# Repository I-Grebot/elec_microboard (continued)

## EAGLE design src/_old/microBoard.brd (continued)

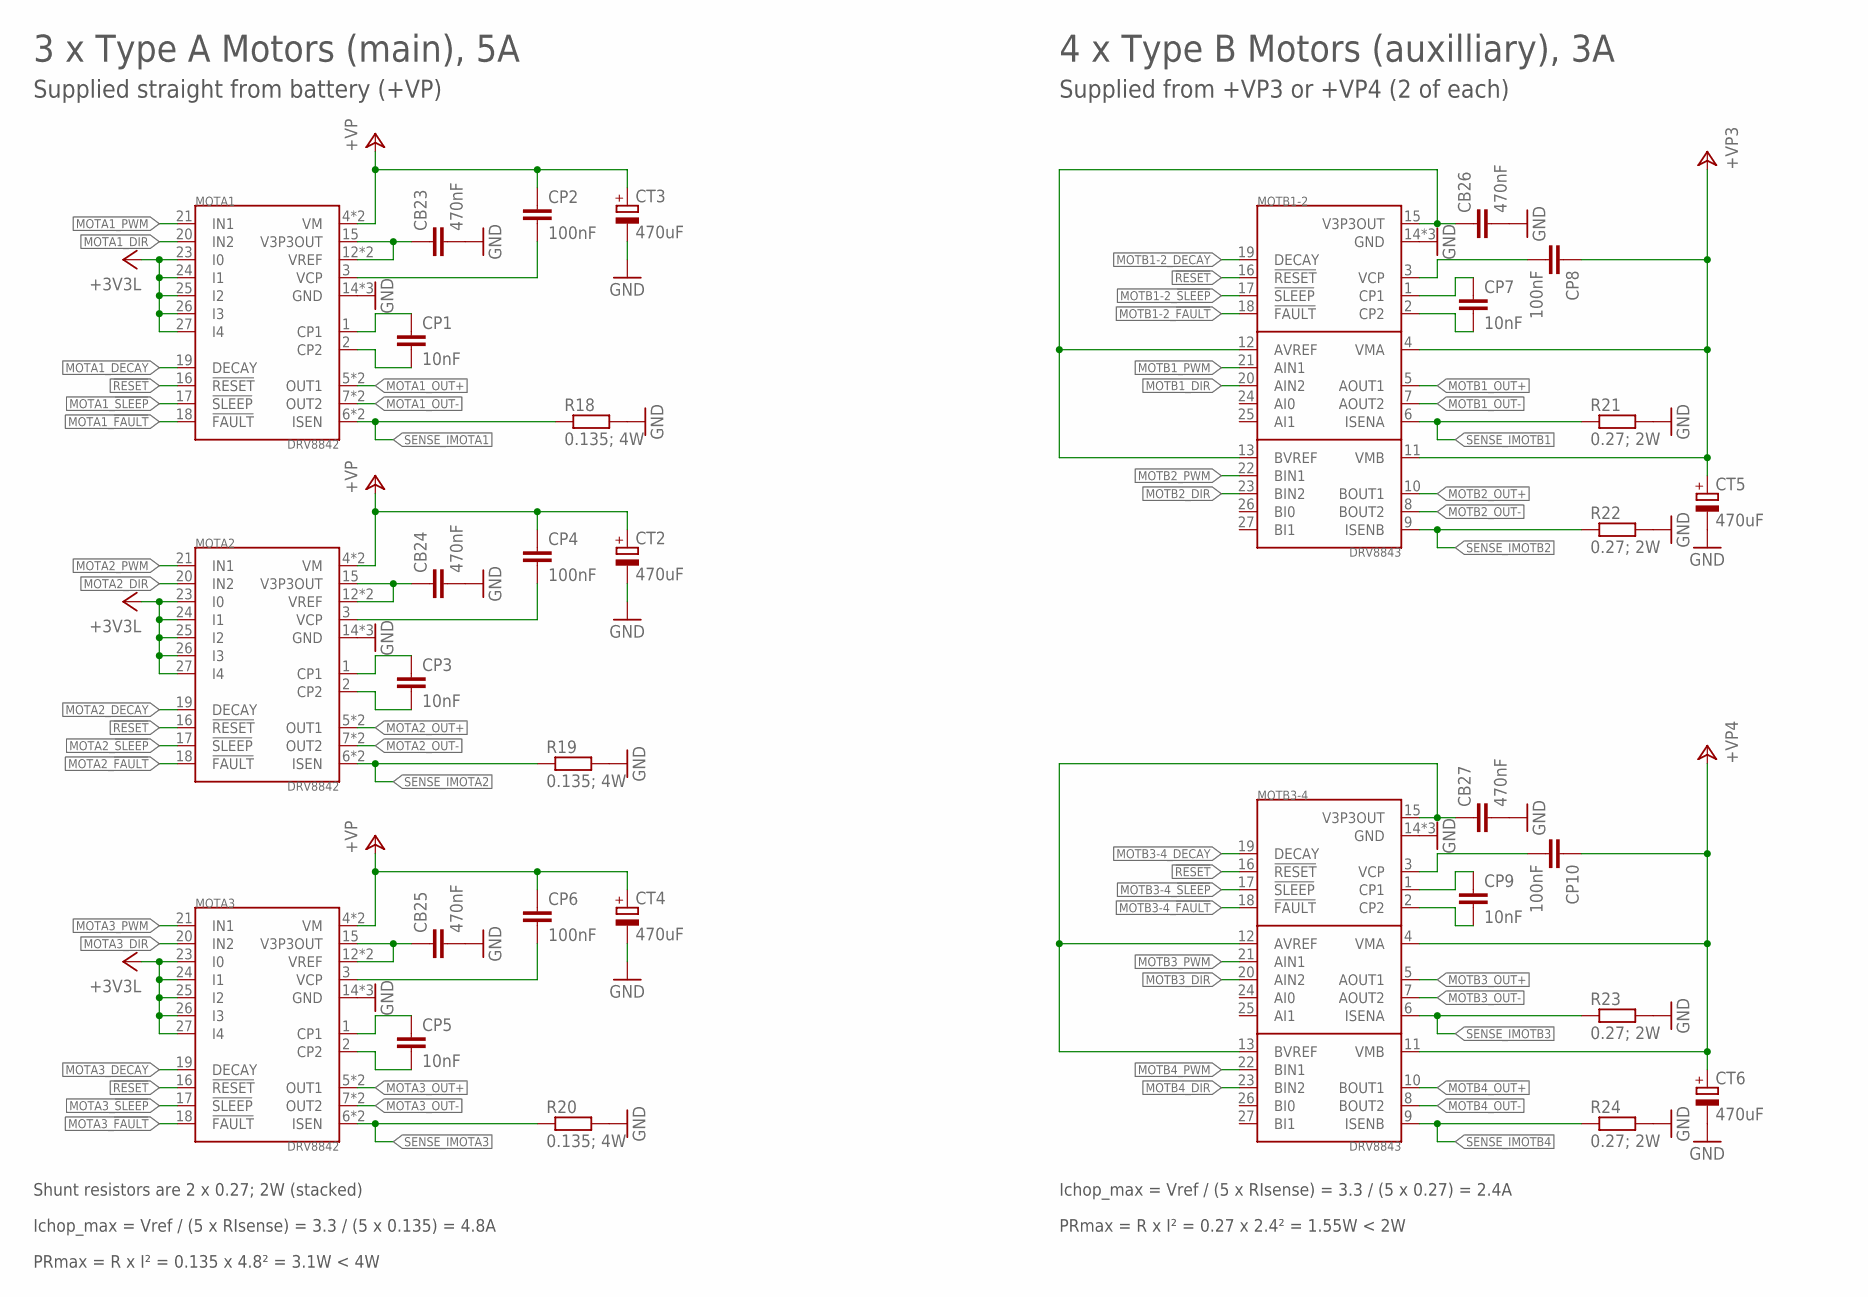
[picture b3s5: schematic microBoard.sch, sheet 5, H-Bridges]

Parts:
CB23, CB24, CB25, CB26, CB27: 470nF; C0603
CP1, CP3, CP5, CP7, CP9: 10nF; C0603
CP2, CP4, CP6, CP8, CP10: 100nF; C0603
CT2, CT3, CT4, CT5, CT6: 470uF; PANASONIC_D
MOTA1, MOTA2, MOTA3: DRV8842; PWP_28
MOTB1-2, MOTB3-4: DRV8843; PWP_28
R18, R19, R20: 0.135; 4W; R2512
R21, R22, R23, R24: 0.27; 2W; R2512

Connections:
!RESET!: MOTA1.16 (!RESET!), MOTA2.16 (!RESET!), MOTA3.16 (!RESET!), MOTB1-2.16 (!RESET!), MOTB3-4.16 (!RESET!)
+3V3L: MOTA1.23 (I0), MOTA1.24 (I1), MOTA1.25 (I2), MOTA1.26 (I3), MOTA1.27 (I4), MOTA2.23 (I0), MOTA2.24 (I1), MOTA2.25 (I2), MOTA2.26 (I3), MOTA2.27 (I4), MOTA3.23 (I0), MOTA3.24 (I1), MOTA3.25 (I2), MOTA3.26 (I3), MOTA3.27 (I4); also elsewhere on the board
+VP: CP2.1, CP4.1, CP6.1, CT2.+, CT3.+, CT4.+, MOTA1.4 (VM), MOTA1.11 (VM), MOTA2.4 (VM), MOTA2.11 (VM), MOTA3.4 (VM), MOTA3.11 (VM); also elsewhere on the board
+VP3: CP8.1, CT5.+, MOTB1-2.4 (VMA), MOTB1-2.11 (VMB); also elsewhere on the board
+VP4: CP10.1, CT6.+, MOTB3-4.4 (VMA), MOTB3-4.11 (VMB); also elsewhere on the board
GND: CB23.2, CB24.2, CB25.2, CB26.2, CB27.2, CT2.-, CT3.-, CT4.-, CT5.-, CT6.-, MOTA1.14 (GND), MOTA1.28 (GND), MOTA1.PPAD (GND), MOTA2.14 (GND), MOTA2.28 (GND), MOTA2.PPAD (GND), MOTA3.14 (GND), MOTA3.28 (GND), MOTA3.PPAD (GND), MOTB1-2.14 (GND), MOTB1-2.28 (GND), MOTB1-2.PPAD (GND), MOTB3-4.14 (GND), MOTB3-4.28 (GND), MOTB3-4.PPAD (GND), R18.2, R19.2, R20.2, R21.2, R22.2, R23.2, R24.2; also elsewhere on the board
MOTA1_!FAULT!: MOTA1.18 (!FAULT!); also elsewhere on the board
MOTA1_!SLEEP!: MOTA1.17 (!SLEEP!)
MOTA1_DECAY: MOTA1.19 (DECAY)
MOTA1_DIR: MOTA1.20 (IN2)
MOTA1_OUT+: MOTA1.5 (OUT1), MOTA1.10 (OUT1)
MOTA1_OUT-: MOTA1.7 (OUT2), MOTA1.8 (OUT2)
MOTA1_PWM: MOTA1.21 (IN1); also elsewhere on the board
MOTA2_!FAULT!: MOTA2.18 (!FAULT!); also elsewhere on the board
MOTA2_!SLEEP!: MOTA2.17 (!SLEEP!)
MOTA2_DECAY: MOTA2.19 (DECAY)
MOTA2_DIR: MOTA2.20 (IN2)
MOTA2_OUT+: MOTA2.5 (OUT1), MOTA2.10 (OUT1)
MOTA2_OUT-: MOTA2.7 (OUT2), MOTA2.8 (OUT2)
MOTA2_PWM: MOTA2.21 (IN1); also elsewhere on the board
MOTA3_!FAULT!: MOTA3.18 (!FAULT!); also elsewhere on the board
MOTA3_!SLEEP!: MOTA3.17 (!SLEEP!)
MOTA3_DECAY: MOTA3.19 (DECAY)
MOTA3_DIR: MOTA3.20 (IN2)
MOTA3_OUT+: MOTA3.5 (OUT1), MOTA3.10 (OUT1)
MOTA3_OUT-: MOTA3.7 (OUT2), MOTA3.8 (OUT2)
MOTA3_PWM: MOTA3.21 (IN1); also elsewhere on the board
MOTB1-2_!FAULT!: MOTB1-2.18 (!FAULT!); also elsewhere on the board
MOTB1-2_!SLEEP!: MOTB1-2.17 (!SLEEP!)
MOTB1-2_DECAY: MOTB1-2.19 (DECAY)
MOTB1_DIR: MOTB1-2.20 (AIN2)
MOTB1_OUT+: MOTB1-2.5 (AOUT1)
MOTB1_OUT-: MOTB1-2.7 (AOUT2)
MOTB1_PWM: MOTB1-2.21 (AIN1); also elsewhere on the board
MOTB2_DIR: MOTB1-2.23 (BIN2)
MOTB2_OUT+: MOTB1-2.10 (BOUT1)
MOTB2_OUT-: MOTB1-2.8 (BOUT2)
MOTB2_PWM: MOTB1-2.22 (BIN1); also elsewhere on the board
MOTB3-4_!FAULT!: MOTB3-4.18 (!FAULT!); also elsewhere on the board
MOTB3-4_!SLEEP!: MOTB3-4.17 (!SLEEP!)
MOTB3-4_DECAY: MOTB3-4.19 (DECAY)
MOTB3_DIR: MOTB3-4.20 (AIN2)
MOTB3_OUT+: MOTB3-4.5 (AOUT1)
MOTB3_OUT-: MOTB3-4.7 (AOUT2)
MOTB3_PWM: MOTB3-4.21 (AIN1); also elsewhere on the board
MOTB4_DIR: MOTB3-4.23 (BIN2)
MOTB4_OUT+: MOTB3-4.10 (BOUT1)
MOTB4_OUT-: MOTB3-4.8 (BOUT2)
MOTB4_PWM: MOTB3-4.22 (BIN1); also elsewhere on the board
unnamed: CP3.1, MOTA2.1 (CP1)
unnamed: CP3.2, MOTA2.2 (CP2)
unnamed: CP1.1, MOTA1.1 (CP1)
unnamed: CP1.2, MOTA1.2 (CP2)
unnamed: CP2.2, MOTA1.3 (VCP)
unnamed: CB23.1, MOTA1.12 (VREF), MOTA1.13 (VREF), MOTA1.15 (V3P3OUT)
unnamed: CP4.2, MOTA2.3 (VCP)
unnamed: CB24.1, MOTA2.12 (VREF), MOTA2.13 (VREF), MOTA2.15 (V3P3OUT)
unnamed: CP5.1, MOTA3.1 (CP1)
unnamed: CP5.2, MOTA3.2 (CP2)
unnamed: CP6.2, MOTA3.3 (VCP)
unnamed: CB25.1, MOTA3.12 (VREF), MOTA3.13 (VREF), MOTA3.15 (V3P3OUT)
unnamed: CP7.2, MOTB1-2.2 (CP2)
unnamed: CP7.1, MOTB1-2.1 (CP1)
unnamed: CP8.2, MOTB1-2.3 (VCP)
unnamed: CB26.1, MOTB1-2.12 (AVREF), MOTB1-2.13 (BVREF), MOTB1-2.15 (V3P3OUT)
unnamed: CP9.2, MOTB3-4.2 (CP2)
unnamed: CP9.1, MOTB3-4.1 (CP1)
unnamed: CP10.2, MOTB3-4.3 (VCP)
unnamed: CB27.1, MOTB3-4.12 (AVREF), MOTB3-4.13 (BVREF), MOTB3-4.15 (V3P3OUT)
SENSE_IMOTA1: MOTA1.6 (ISEN), MOTA1.9 (ISEN), R18.1; also elsewhere on the board
SENSE_IMOTA2: MOTA2.6 (ISEN), MOTA2.9 (ISEN), R19.1; also elsewhere on the board
SENSE_IMOTA3: MOTA3.6 (ISEN), MOTA3.9 (ISEN), R20.1; also elsewhere on the board
SENSE_IMOTB1: MOTB1-2.6 (ISENA), R21.1; also elsewhere on the board
SENSE_IMOTB2: MOTB1-2.9 (ISENB), R22.1; also elsewhere on the board
SENSE_IMOTB3: MOTB3-4.6 (ISENA), R23.1; also elsewhere on the board
SENSE_IMOTB4: MOTB3-4.9 (ISENB), R24.1; also elsewhere on the board

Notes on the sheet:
3 x Type A Motors (main), 5A
Ichop_max = Vref / (5 x RIsense) = 3.3 / (5 x 0.135) = 4.8A
Ichop_max = Vref / (5 x RIsense) = 3.3 / (5 x 0.27) = 2.4A
PRmax = R x I² = 0.27 x 2.4² = 1.55W < 2W
PRmax = R x I² = 0.135 x 4.8² = 3.1W < 4W
Shunt resistors are 2 x 0.27; 2W (stacked)
4 x Type B Motors (auxilliary), 3A
Supplied straight from battery (+VP)
Supplied from +VP3 or +VP4 (2 of each)

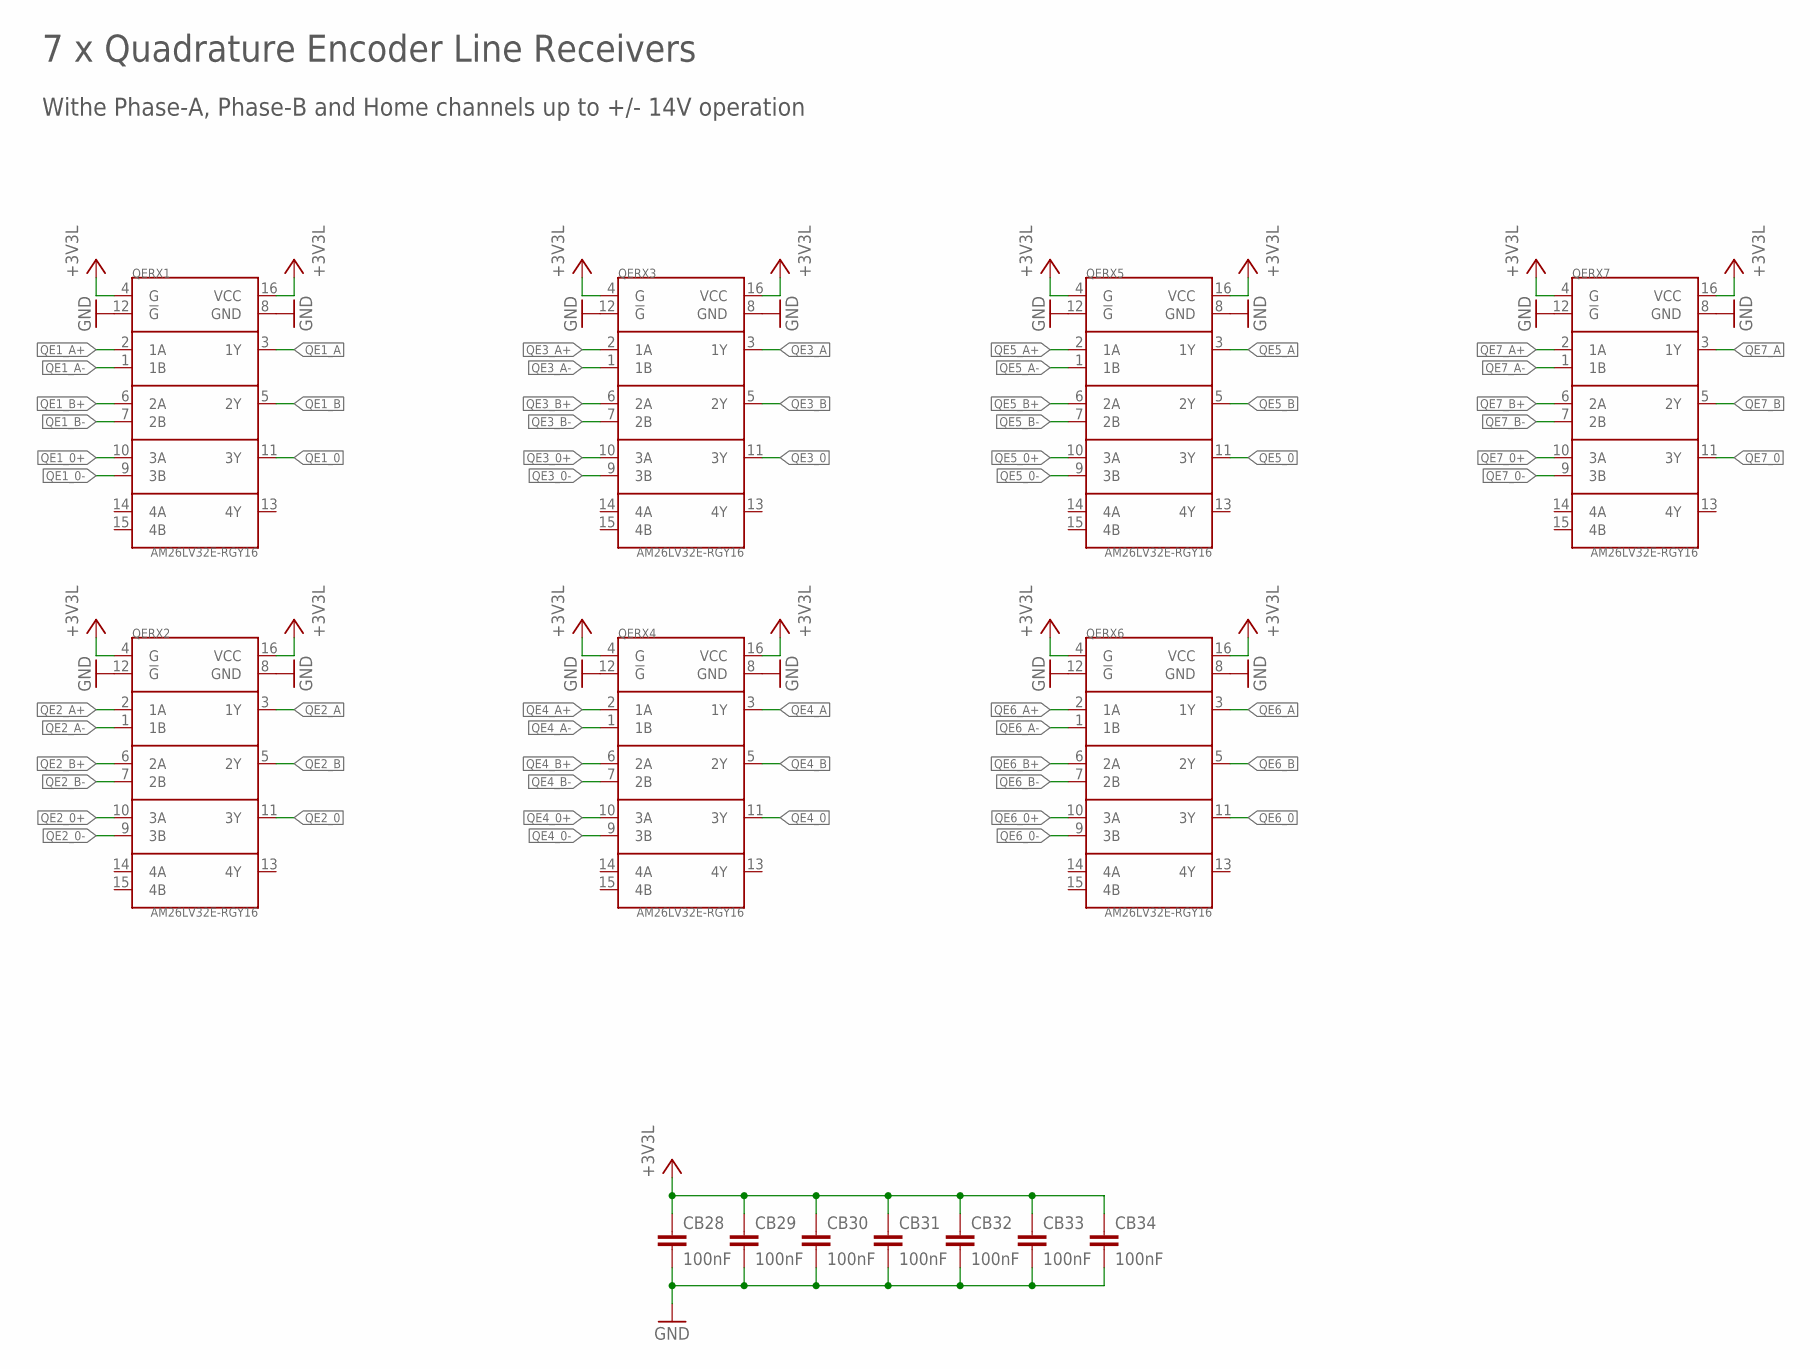
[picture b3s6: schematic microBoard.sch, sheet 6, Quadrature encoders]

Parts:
CB28, CB29, CB30, CB31, CB32, CB33, CB34: 100nF; C0603
QERX1, QERX2, QERX3, QERX4, QERX5, QERX6, QERX7: AM26LV32E-RGY16; RGY_16

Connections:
+3V3L: CB28.1, CB29.1, CB30.1, CB31.1, CB32.1, CB33.1, CB34.1, QERX1.4 (G), QERX1.16 (VCC), QERX2.4 (G), QERX2.16 (VCC), QERX3.4 (G), QERX3.16 (VCC), QERX4.4 (G), QERX4.16 (VCC), QERX5.4 (G), QERX5.16 (VCC), QERX6.4 (G), QERX6.16 (VCC), QERX7.4 (G), QERX7.16 (VCC); also elsewhere on the board
GND: CB28.2, CB29.2, CB30.2, CB31.2, CB32.2, CB33.2, CB34.2, QERX1.8 (GND), QERX1.12 (!G!), QERX2.8 (GND), QERX2.12 (!G!), QERX3.8 (GND), QERX3.12 (!G!), QERX4.8 (GND), QERX4.12 (!G!), QERX5.8 (GND), QERX5.12 (!G!), QERX6.8 (GND), QERX6.12 (!G!), QERX7.8 (GND), QERX7.12 (!G!); also elsewhere on the board
QE1_0: QERX1.11 (3Y)
QE1_0+: QERX1.10 (3A); also elsewhere on the board
QE1_0-: QERX1.9 (3B); also elsewhere on the board
QE1_A: QERX1.3 (1Y)
QE1_A+: QERX1.2 (1A); also elsewhere on the board
QE1_A-: QERX1.1 (1B); also elsewhere on the board
QE1_B: QERX1.5 (2Y)
QE1_B+: QERX1.6 (2A); also elsewhere on the board
QE1_B-: QERX1.7 (2B); also elsewhere on the board
QE2_0: QERX2.11 (3Y)
QE2_0+: QERX2.10 (3A); also elsewhere on the board
QE2_0-: QERX2.9 (3B); also elsewhere on the board
QE2_A: QERX2.3 (1Y)
QE2_A+: QERX2.2 (1A); also elsewhere on the board
QE2_A-: QERX2.1 (1B); also elsewhere on the board
QE2_B: QERX2.5 (2Y)
QE2_B+: QERX2.6 (2A); also elsewhere on the board
QE2_B-: QERX2.7 (2B); also elsewhere on the board
QE3_0: QERX3.11 (3Y)
QE3_0+: QERX3.10 (3A); also elsewhere on the board
QE3_0-: QERX3.9 (3B); also elsewhere on the board
QE3_A: QERX3.3 (1Y)
QE3_A+: QERX3.2 (1A); also elsewhere on the board
QE3_A-: QERX3.1 (1B); also elsewhere on the board
QE3_B: QERX3.5 (2Y)
QE3_B+: QERX3.6 (2A); also elsewhere on the board
QE3_B-: QERX3.7 (2B); also elsewhere on the board
QE4_0: QERX4.11 (3Y)
QE4_0+: QERX4.10 (3A); also elsewhere on the board
QE4_0-: QERX4.9 (3B); also elsewhere on the board
QE4_A: QERX4.3 (1Y)
QE4_A+: QERX4.2 (1A); also elsewhere on the board
QE4_A-: QERX4.1 (1B); also elsewhere on the board
QE4_B: QERX4.5 (2Y)
QE4_B+: QERX4.6 (2A); also elsewhere on the board
QE4_B-: QERX4.7 (2B); also elsewhere on the board
QE5_0: QERX5.11 (3Y)
QE5_0+: QERX5.10 (3A); also elsewhere on the board
QE5_0-: QERX5.9 (3B); also elsewhere on the board
QE5_A: QERX5.3 (1Y)
QE5_A+: QERX5.2 (1A); also elsewhere on the board
QE5_A-: QERX5.1 (1B); also elsewhere on the board
QE5_B: QERX5.5 (2Y)
QE5_B+: QERX5.6 (2A); also elsewhere on the board
QE5_B-: QERX5.7 (2B); also elsewhere on the board
QE6_0: QERX6.11 (3Y)
QE6_0+: QERX6.10 (3A); also elsewhere on the board
QE6_0-: QERX6.9 (3B); also elsewhere on the board
QE6_A: QERX6.3 (1Y)
QE6_A+: QERX6.2 (1A); also elsewhere on the board
QE6_A-: QERX6.1 (1B); also elsewhere on the board
QE6_B: QERX6.5 (2Y)
QE6_B+: QERX6.6 (2A); also elsewhere on the board
QE6_B-: QERX6.7 (2B); also elsewhere on the board
QE7_0: QERX7.11 (3Y)
QE7_0+: QERX7.10 (3A); also elsewhere on the board
QE7_0-: QERX7.9 (3B); also elsewhere on the board
QE7_A: QERX7.3 (1Y)
QE7_A+: QERX7.2 (1A); also elsewhere on the board
QE7_A-: QERX7.1 (1B); also elsewhere on the board
QE7_B: QERX7.5 (2Y)
QE7_B+: QERX7.6 (2A); also elsewhere on the board
QE7_B-: QERX7.7 (2B); also elsewhere on the board

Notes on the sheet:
7 x Quadrature Encoder Line Receivers
Withe Phase-A, Phase-B and Home channels up to +/- 14V operation

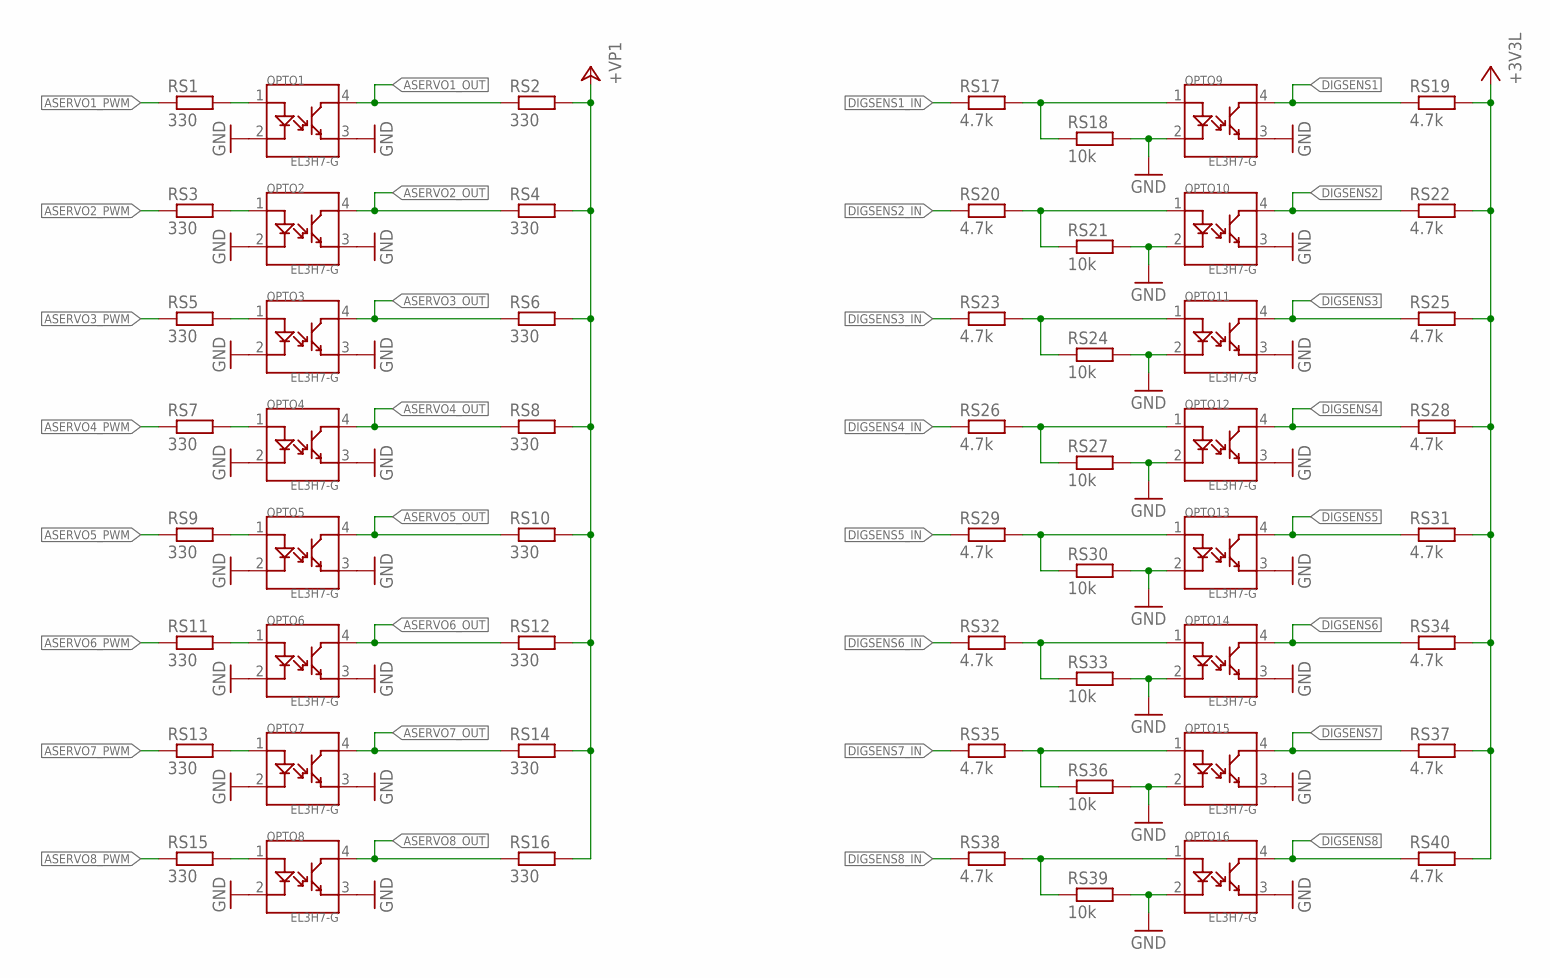
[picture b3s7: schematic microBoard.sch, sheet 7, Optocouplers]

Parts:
OPTO1, OPTO2, OPTO3, OPTO4, OPTO5, OPTO6, OPTO7, OPTO8, OPTO9, OPTO10, OPTO11, OPTO12, OPTO13, OPTO14, OPTO15, OPTO16: EL3H7-G; SSOP_4
RS1, RS2, RS3, RS4, RS5, RS6, RS7, RS8, RS9, RS10, RS11, RS12, RS13, RS14, RS15, RS16: 330; R0603
RS17, RS19, RS20, RS22, RS23, RS25, RS26, RS28, RS29, RS31, RS32, RS34, RS35, RS37, RS38, RS40: 4.7k; R0603
RS18, RS21, RS24, RS27, RS30, RS33, RS36, RS39: 10k; R0603

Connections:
+3V3L: RS19.2, RS22.2, RS25.2, RS28.2, RS31.2, RS34.2, RS37.2, RS40.2; also elsewhere on the board
+VP1: RS2.2, RS4.2, RS6.2, RS8.2, RS10.2, RS12.2, RS14.2, RS16.2; also elsewhere on the board
ASERVO1_OUT: OPTO1.4, RS2.1
ASERVO1_PWM: RS1.1
ASERVO2_OUT: OPTO2.4, RS4.1
ASERVO2_PWM: RS3.1
ASERVO3_OUT: OPTO3.4, RS6.1
ASERVO3_PWM: RS5.1
ASERVO4_OUT: OPTO4.4, RS8.1
ASERVO4_PWM: RS7.1
ASERVO5_OUT: OPTO5.4, RS10.1
ASERVO5_PWM: RS9.1
ASERVO6_OUT: OPTO6.4, RS12.1
ASERVO6_PWM: RS11.1
ASERVO7_OUT: OPTO7.4, RS14.1
ASERVO7_PWM: RS13.1
ASERVO8_OUT: OPTO8.4, RS16.1
ASERVO8_PWM: RS15.1
DIGSENS1: OPTO9.4, RS19.1
DIGSENS1_IN: RS17.1
DIGSENS2: OPTO10.4, RS22.1
DIGSENS2_IN: RS20.1
DIGSENS3: OPTO11.4, RS25.1
DIGSENS3_IN: RS23.1
DIGSENS4: OPTO12.4, RS28.1
DIGSENS4_IN: RS26.1
DIGSENS5: OPTO13.4, RS31.1
DIGSENS5_IN: RS29.1
DIGSENS6: OPTO14.4, RS34.1
DIGSENS6_IN: RS32.1
DIGSENS7: OPTO15.4, RS37.1
DIGSENS7_IN: RS35.1
DIGSENS8: OPTO16.4, RS40.1
DIGSENS8_IN: RS38.1
GND: OPTO1.2, OPTO1.3, OPTO2.2, OPTO2.3, OPTO3.2, OPTO3.3, OPTO4.2, OPTO4.3, OPTO5.2, OPTO5.3, OPTO6.2, OPTO6.3, OPTO7.2, OPTO7.3, OPTO8.2, OPTO8.3, OPTO9.2, OPTO9.3, OPTO10.2, OPTO10.3, OPTO11.2, OPTO11.3, OPTO12.2, OPTO12.3, OPTO13.2, OPTO13.3, OPTO14.2, OPTO14.3, OPTO15.2, OPTO15.3, OPTO16.2, OPTO16.3, RS18.2, RS21.2, RS24.2, RS27.2, RS30.2, RS33.2, RS36.2, RS39.2; also elsewhere on the board
unnamed: OPTO1.1, RS1.2
unnamed: OPTO2.1, RS3.2
unnamed: OPTO3.1, RS5.2
unnamed: OPTO4.1, RS7.2
unnamed: OPTO5.1, RS9.2
unnamed: OPTO6.1, RS11.2
unnamed: OPTO7.1, RS13.2
unnamed: OPTO8.1, RS15.2
unnamed: OPTO9.1, RS17.2, RS18.1
unnamed: OPTO11.1, RS23.2, RS24.1
unnamed: OPTO10.1, RS20.2, RS21.1
unnamed: OPTO12.1, RS26.2, RS27.1
unnamed: OPTO13.1, RS29.2, RS30.1
unnamed: OPTO14.1, RS32.2, RS33.1
unnamed: OPTO15.1, RS35.2, RS36.1
unnamed: OPTO16.1, RS38.2, RS39.1

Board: 2 copper layers, 227 parts (0 on the bottom side), 180 nets, no tracks yet.

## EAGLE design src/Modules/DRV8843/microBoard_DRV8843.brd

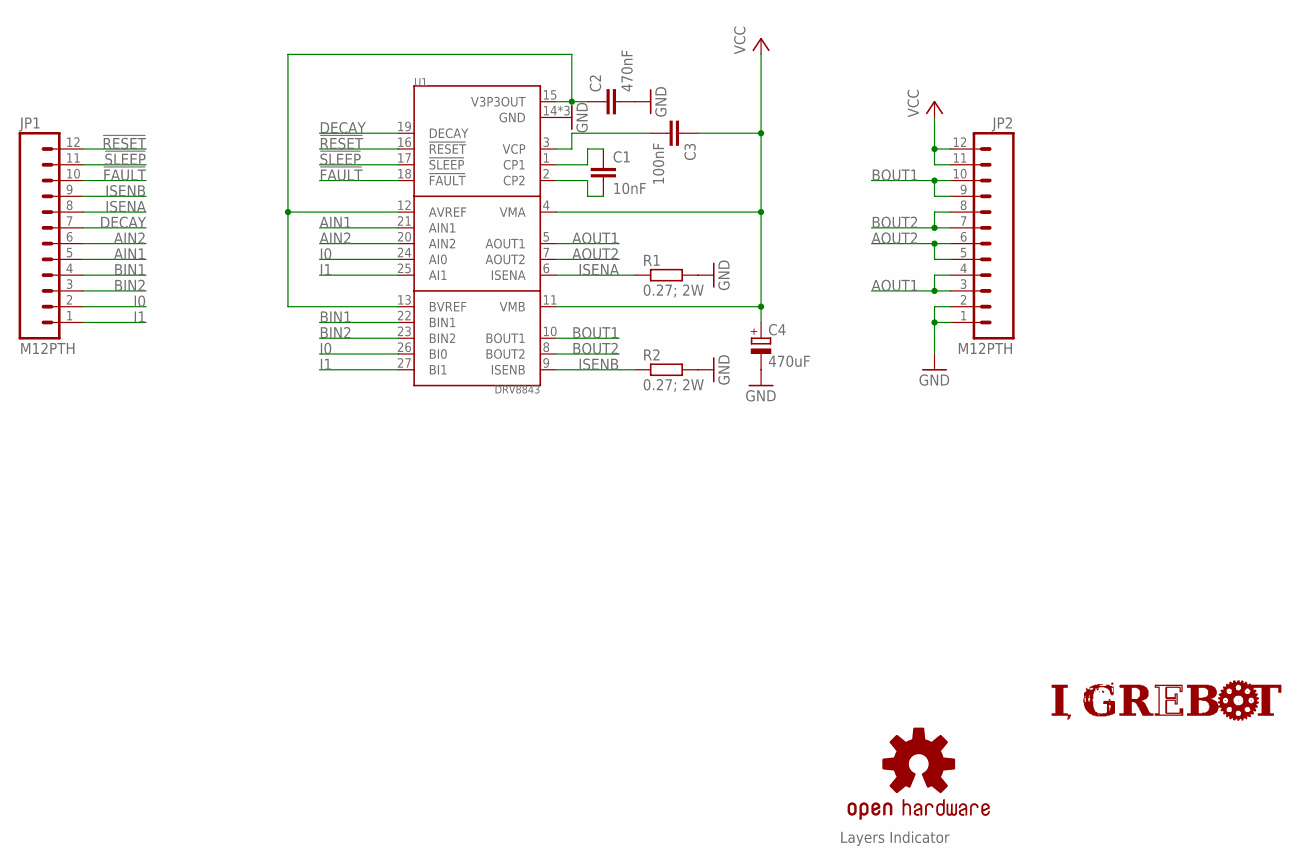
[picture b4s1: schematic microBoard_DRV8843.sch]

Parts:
C1: 10nF; C0603
C2: 470nF; C0603
C3: 100nF; C0603
C4: 470uF; PANASONIC_D
JP1, JP2: M12PTH; 1X12
LOGO1: OSHW-LOGOS; OSHW-LOGO-S
R1, R2: 0.27; 2W; R2010
U1: DRV8843; PWP_28
U$1: LOGO_IGREBOT12X2MM; IGREBOT_12X2MM
U$2: LAYERS_CHECK4_LAYERS; LAYERS_CHECK_4

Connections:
!FAULT!: JP1.10, U1.18 (!FAULT!)
!RESET!: JP1.12, U1.16 (!RESET!)
!SLEEP!: JP1.11, U1.17 (!SLEEP!)
AIN1: JP1.5, U1.21 (AIN1)
AIN2: JP1.6, U1.20 (AIN2)
AOUT1: JP2.3, JP2.4, U1.5 (AOUT1)
AOUT2: JP2.5, JP2.6, U1.7 (AOUT2)
BIN1: JP1.4, U1.22 (BIN1)
BIN2: JP1.3, U1.23 (BIN2)
BOUT1: JP2.9, JP2.10, U1.10 (BOUT1)
BOUT2: JP2.7, JP2.8, U1.8 (BOUT2)
DECAY: JP1.7, U1.19 (DECAY)
GND: C2.2, C4.-, JP2.1, JP2.2, R1.2, R2.2, U1.14 (GND), U1.28 (GND), U1.PPAD (GND)
I0: JP1.2, U1.24 (AI0), U1.26 (BI0)
I1: JP1.1, U1.25 (AI1), U1.27 (BI1)
ISENA: JP1.8, R1.1, U1.6 (ISENA)
ISENB: JP1.9, R2.1, U1.9 (ISENB)
unnamed: C1.2, U1.2 (CP2)
unnamed: C1.1, U1.1 (CP1)
unnamed: C3.2, U1.3 (VCP)
unnamed: C2.1, U1.12 (AVREF), U1.13 (BVREF), U1.15 (V3P3OUT)
VCC: C3.1, C4.+, JP2.11, JP2.12, U1.4 (VMA), U1.11 (VMB)

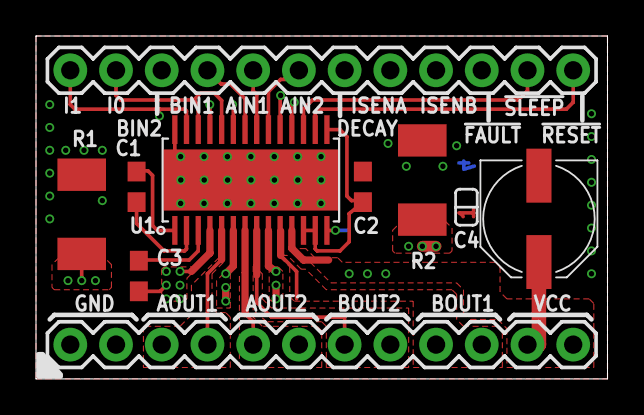
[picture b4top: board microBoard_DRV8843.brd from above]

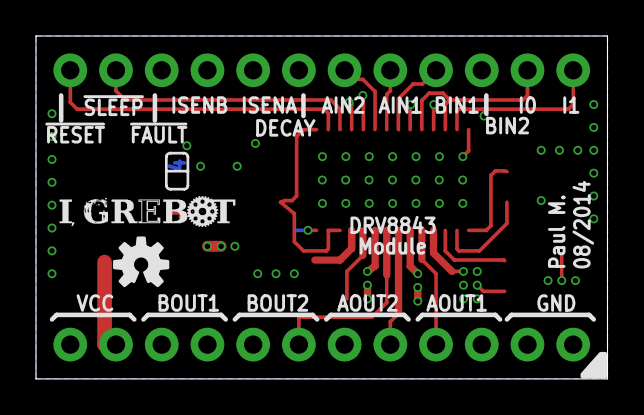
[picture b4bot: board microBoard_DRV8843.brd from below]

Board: 4 copper layers, 31.8 x 19.1 mm, 12 parts (2 on the bottom side), 22 nets.

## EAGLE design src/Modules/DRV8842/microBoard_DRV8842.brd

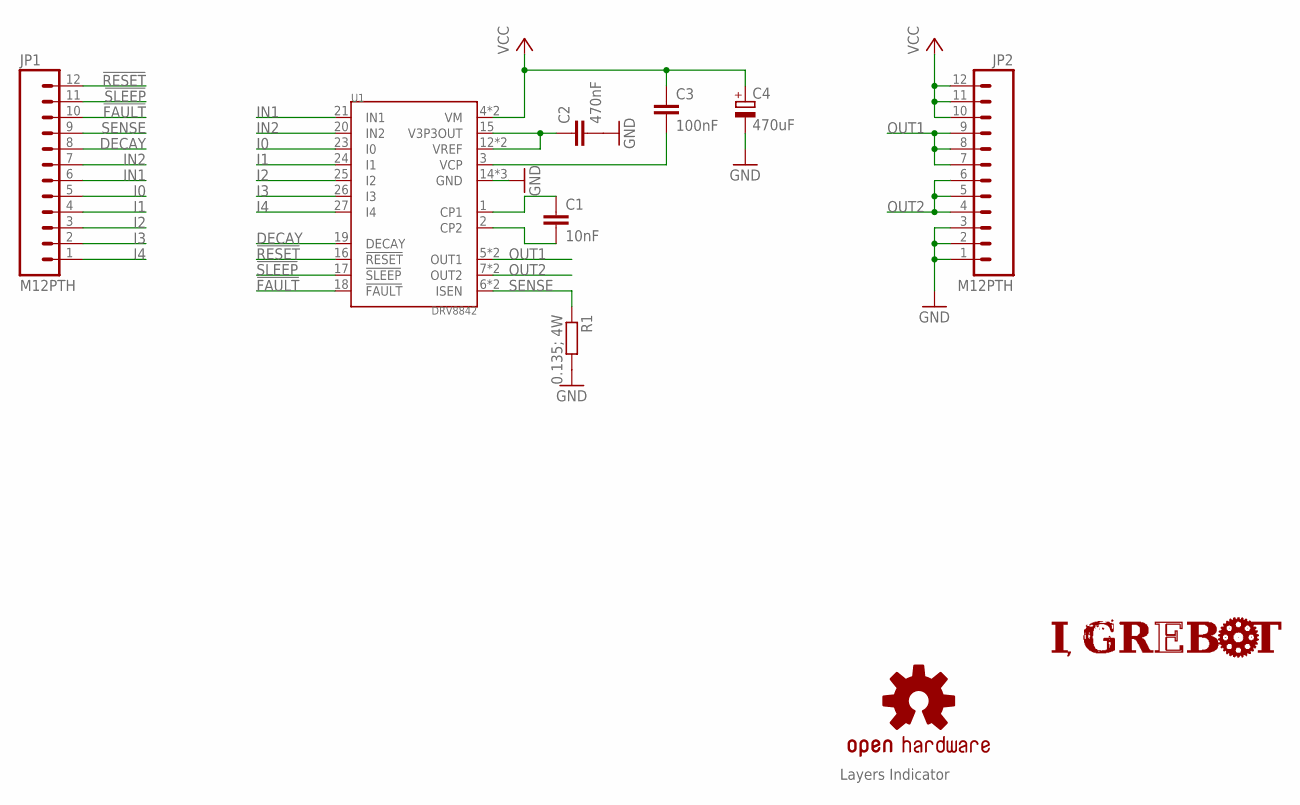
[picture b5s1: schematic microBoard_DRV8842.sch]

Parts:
C1: 10nF; C0603
C2: 470nF; C0603
C3: 100nF; C0603
C4: 470uF; PANASONIC_D
JP1, JP2: M12PTH; 1X12
LOGO1: OSHW-LOGOS; OSHW-LOGO-S
R1: 0.135; 4W; R2010
U1: DRV8842; PWP_28
U$1: LOGO_IGREBOT12X2MM; IGREBOT_12X2MM
U$2: LAYERS_CHECK4_LAYERS; LAYERS_CHECK_4

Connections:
!FAULT!: JP1.10, U1.18 (!FAULT!)
!RESET!: JP1.12, U1.16 (!RESET!)
!SLEEP!: JP1.11, U1.17 (!SLEEP!)
DECAY: JP1.8, U1.19 (DECAY)
GND: C2.2, C4.-, JP2.1, JP2.2, JP2.3, R1.2, U1.14 (GND), U1.28 (GND), U1.PPAD (GND)
I0: JP1.5, U1.23 (I0)
I1: JP1.4, U1.24 (I1)
I2: JP1.3, U1.25 (I2)
I3: JP1.2, U1.26 (I3)
I4: JP1.1, U1.27 (I4)
IN1: JP1.6, U1.21 (IN1)
IN2: JP1.7, U1.20 (IN2)
unnamed: C1.1, U1.1 (CP1)
unnamed: C1.2, U1.2 (CP2)
unnamed: C3.2, U1.3 (VCP)
unnamed: C2.1, U1.12 (VREF), U1.13 (VREF), U1.15 (V3P3OUT)
OUT1: JP2.7, JP2.8, JP2.9, U1.5 (OUT1), U1.10 (OUT1)
OUT2: JP2.4, JP2.5, JP2.6, U1.7 (OUT2), U1.8 (OUT2)
SENSE: JP1.9, R1.1, U1.6 (ISEN), U1.9 (ISEN)
VCC: C3.1, C4.+, JP2.10, JP2.11, JP2.12, U1.4 (VM), U1.11 (VM)

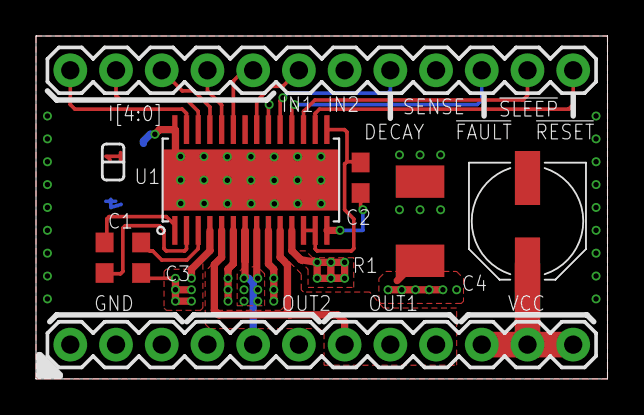
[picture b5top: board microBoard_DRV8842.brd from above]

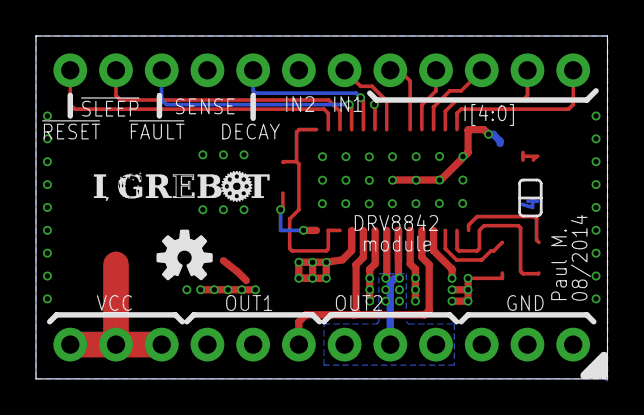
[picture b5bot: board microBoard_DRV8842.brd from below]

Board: 4 copper layers, 31.8 x 19.1 mm, 11 parts (2 on the bottom side), 20 nets.

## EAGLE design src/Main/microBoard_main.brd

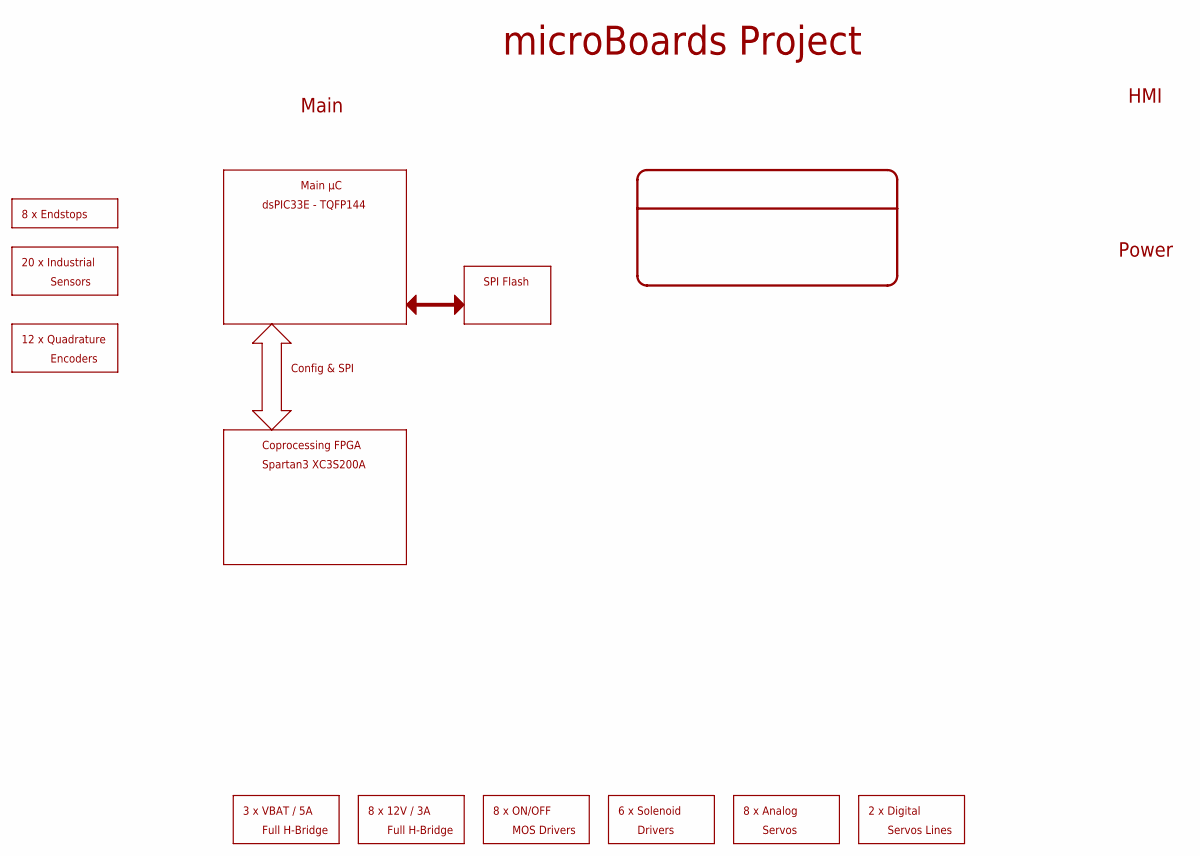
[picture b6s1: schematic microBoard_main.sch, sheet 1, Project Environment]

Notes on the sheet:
microBoards Project
Main
Power
HMI
dsPIC33E - TQFP144
Main µC
Coprocessing FPGA
Spartan3 XC3S200A
SPI Flash
Config & SPI
12 x Quadrature
Encoders
20 x Industrial
Sensors
8 x Endstops
8 x Analog
Servos
2 x Digital
Servos Lines
3 x VBAT / 5A
Full H-Bridge
8 x 12V / 3A
8 x ON/OFF
MOS Drivers
6 x Solenoid
Drivers

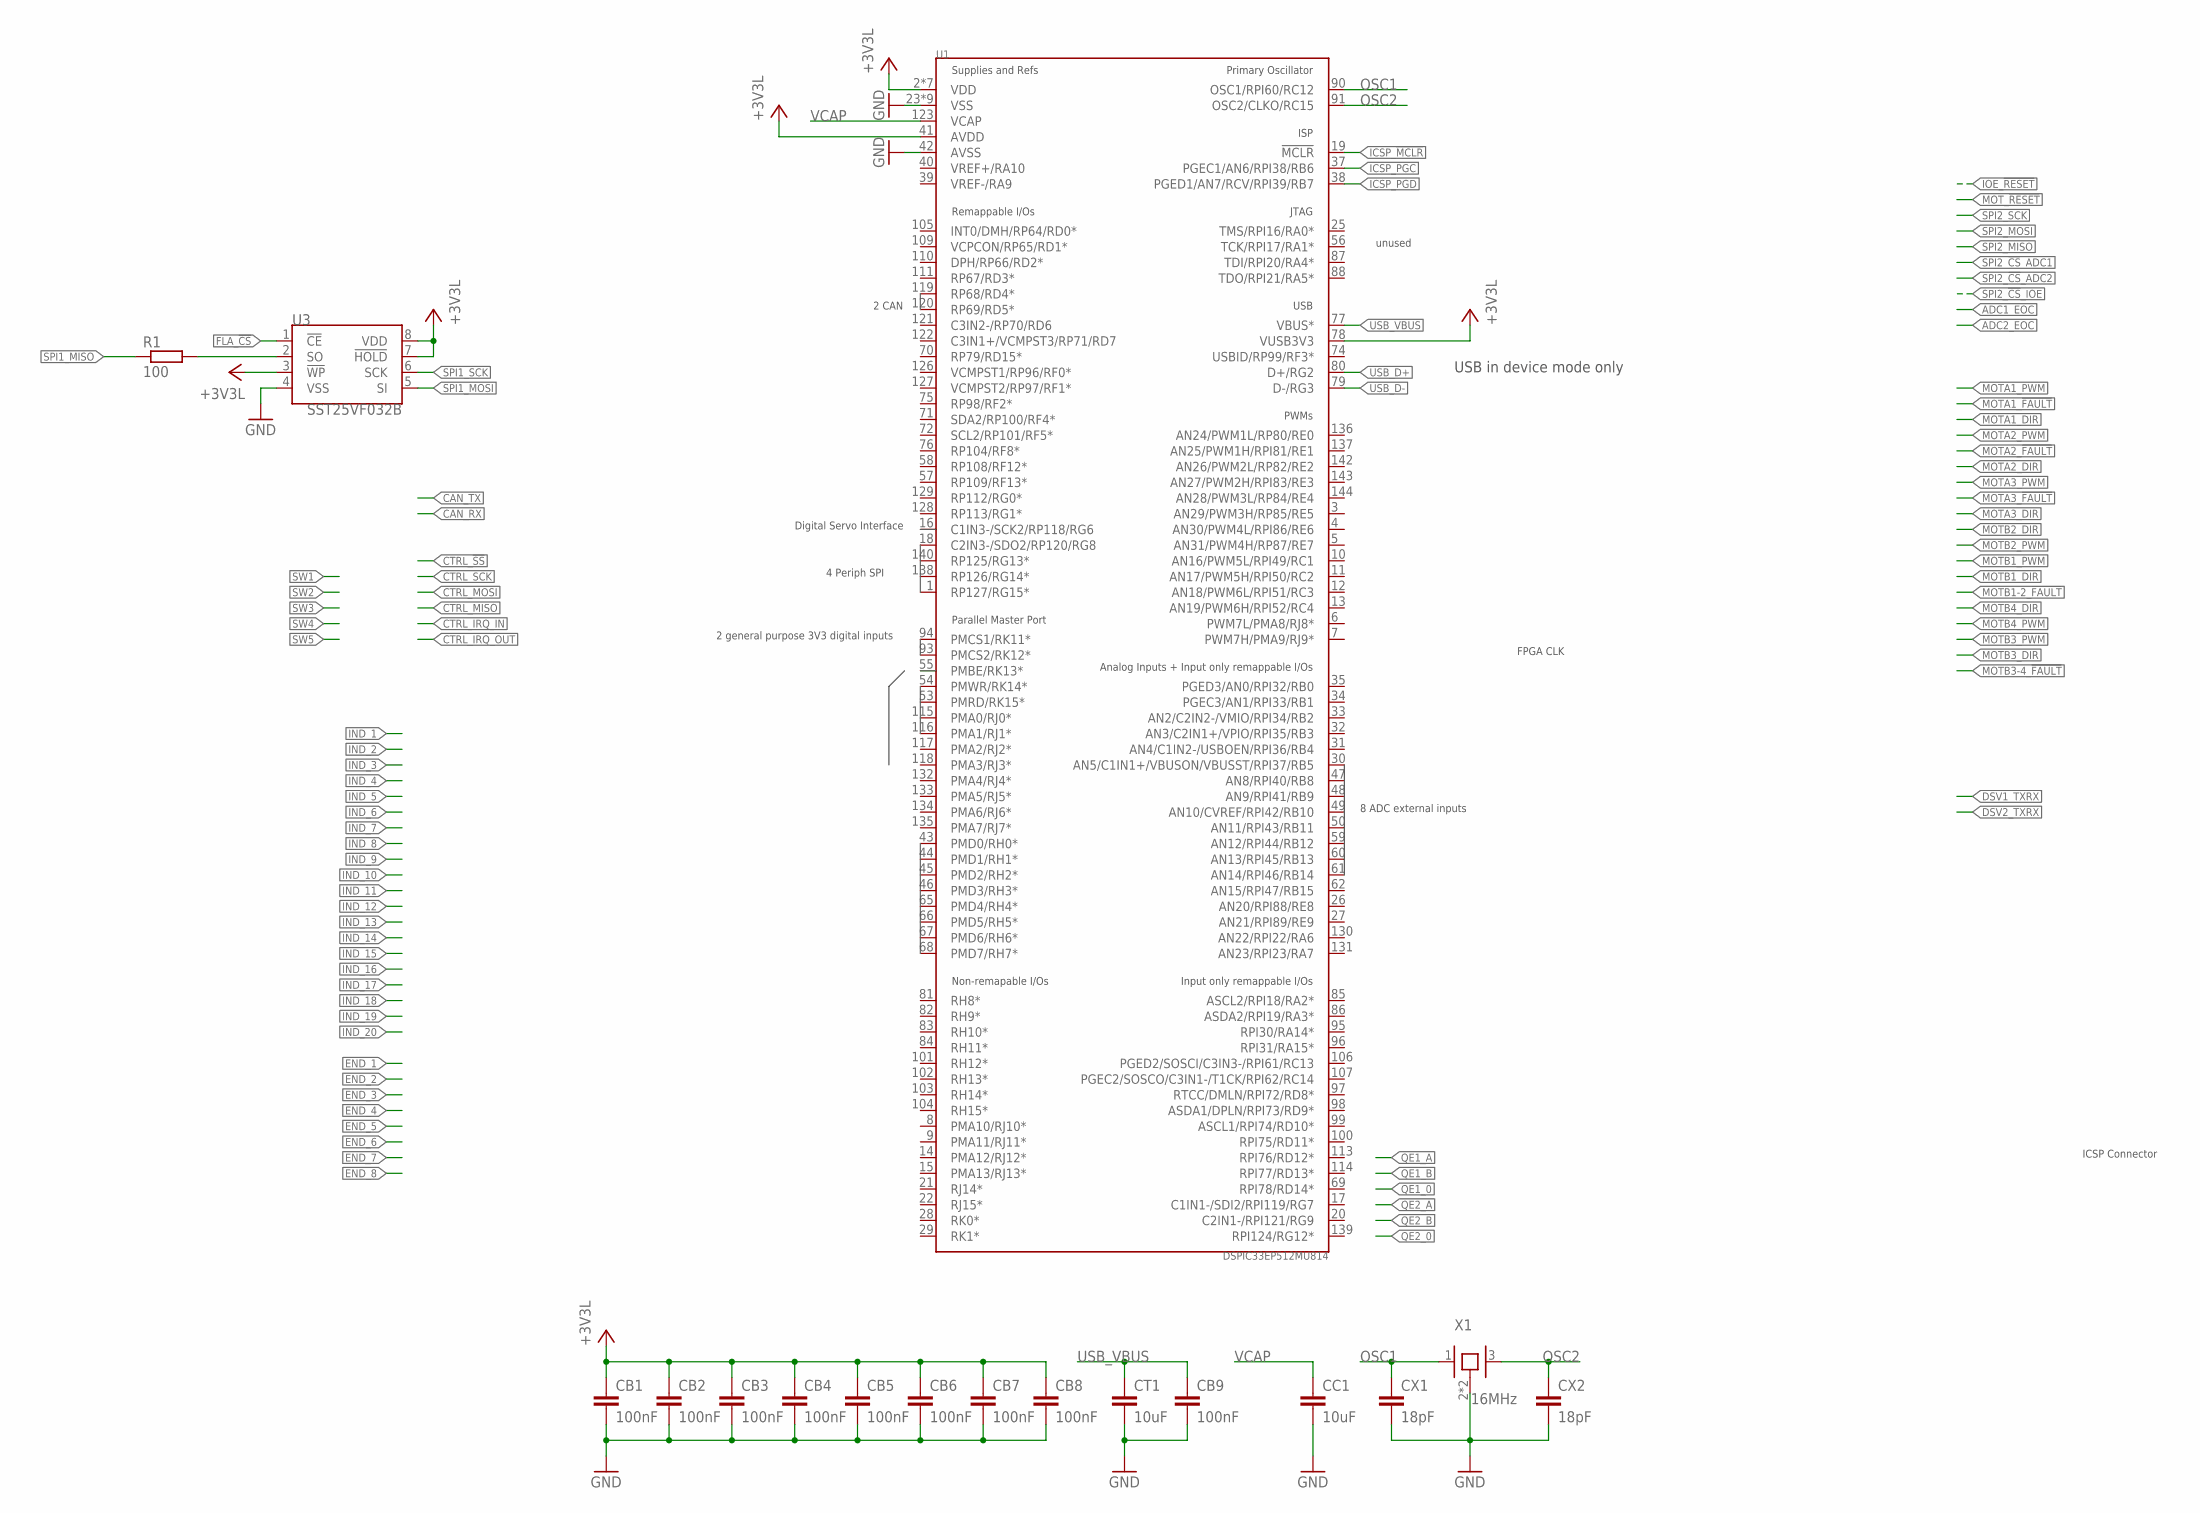
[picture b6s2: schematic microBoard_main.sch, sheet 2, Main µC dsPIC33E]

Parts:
CB1, CB2, CB3, CB4, CB5, CB6, CB7, CB8, CB9: 100nF; C0603
CC1: 10uF; C1210
CT1: 10uF; C1210
CX1, CX2: 18pF; C0603
R1: 100; R0603
U1: DSPIC33EP512MU814; TQFP_144
U3: SST25VF032B; SOIC_8
X1: 16MHz; CRYSTAL-OSC-SMD-5X3

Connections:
+3V3L: CB1.1, CB2.1, CB3.1, CB4.1, CB5.1, CB6.1, CB7.1, CB8.1, U1.2 (VDD), U1.24 (VDD), U1.41 (AVDD), U1.52 (VDD), U1.64 (VDD), U1.78 (VUSB3V3), U1.89 (VDD), U1.112 (VDD), U1.124 (VDD), U3.3 (!WP!), U3.7 (!HOLD!), U3.8 (VDD); also elsewhere on the board
FLA_!CS!: U3.1 (!CE!)
GND: CB1.2, CB2.2, CB3.2, CB4.2, CB5.2, CB6.2, CB7.2, CB8.2, CB9.2, CC1.2, CT1.2, CX1.2, CX2.2, U1.23 (VSS), U1.36 (VSS), U1.42 (AVSS), U1.51 (VSS), U1.63 (VSS), U1.73 (VSS), U1.92 (VSS), U1.108 (VSS), U1.125 (VSS), U1.141 (VSS), U3.4 (VSS), X1.2, X1.4; also elsewhere on the board
ICSP_!MCLR!: U1.19 (!MCLR!); also elsewhere on the board
ICSP_PGC: U1.37 (PGEC1/AN6/RPI38/RB6); also elsewhere on the board
ICSP_PGD: U1.38 (PGED1/AN7/RCV/RPI39/RB7); also elsewhere on the board
unnamed: R1.2, U3.2 (SO)
OSC1: CX1.1, U1.90 (OSC1/RPI60/RC12), X1.1
OSC2: CX2.1, U1.91 (OSC2/CLKO/RC15), X1.3
SPI1_MISO: R1.1
SPI1_MOSI: U3.5 (SI)
SPI1_SCK: U3.6 (SCK)
USB_D+: U1.80 (D+/RG2)
USB_D-: U1.79 (D-/RG3)
USB_VBUS: CB9.1, CT1.1, U1.77 (VBUS*)
VCAP: CC1.1, U1.123 (VCAP)

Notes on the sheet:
USB in device mode only
unused
2 general purpose 3V3 digital inputs
Digital Servo Interface
2 CAN
4 Periph SPI
8 ADC external inputs
FPGA CLK
ICSP Connector
